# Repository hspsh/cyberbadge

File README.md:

# cyberbadge

Pin definitions:

| Name        | Pin         | Description
| ----------- | ----------- | -----------
| ESP_BOOT_B1 | 0           | Sleep / User button 1 / boot into programming mode
| PROG_TX     | 1           | 
| PROG_RX     | 3           | 
| LIPO_VMEAS  | 15          | Connected to LiPo voltage behind 2/3 divider
| WS_OUT      | 22          | WS2812 output pin
| ESP_B2      | 26          | User button 2 / boot alternative firmware
| ESP_B3      | 25          | User button 3

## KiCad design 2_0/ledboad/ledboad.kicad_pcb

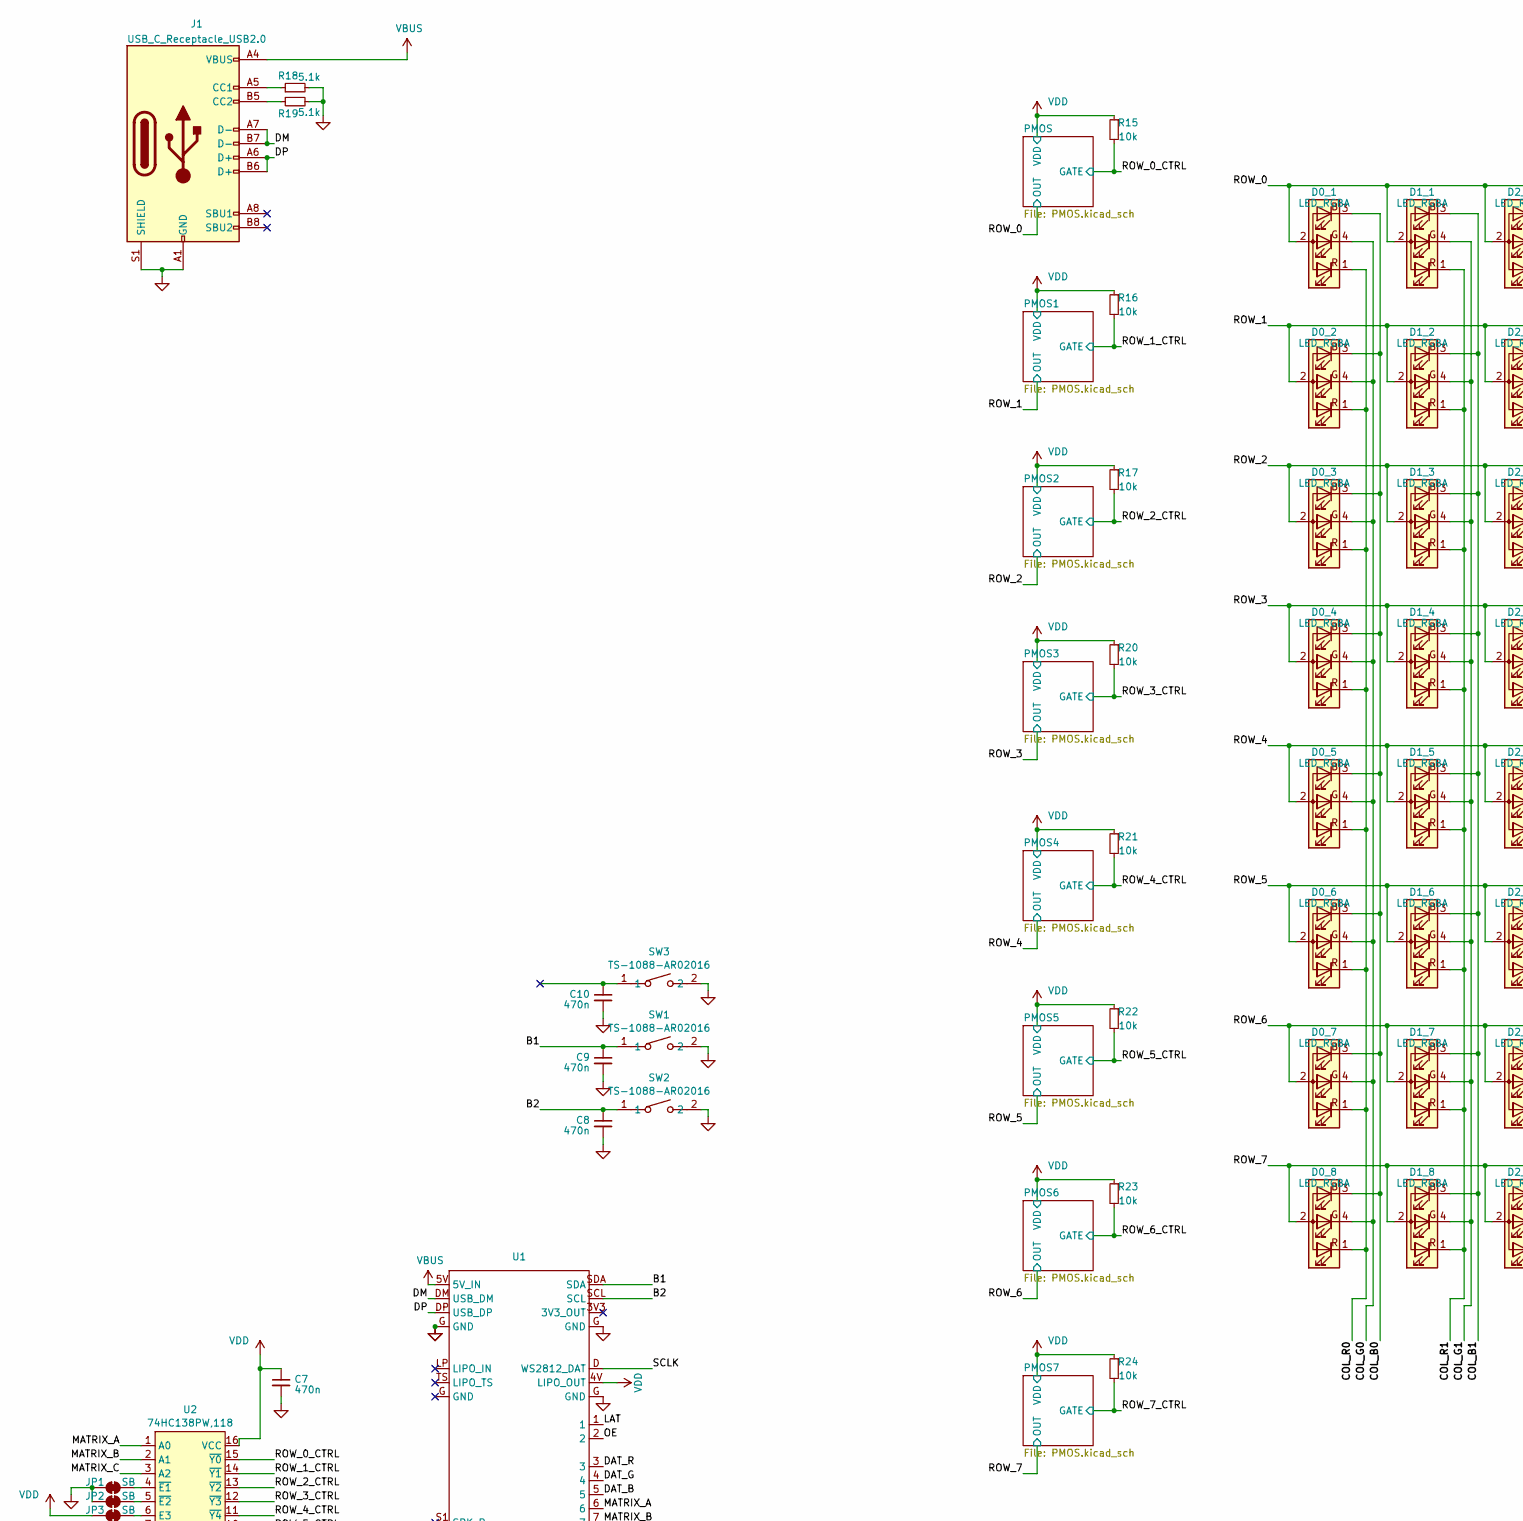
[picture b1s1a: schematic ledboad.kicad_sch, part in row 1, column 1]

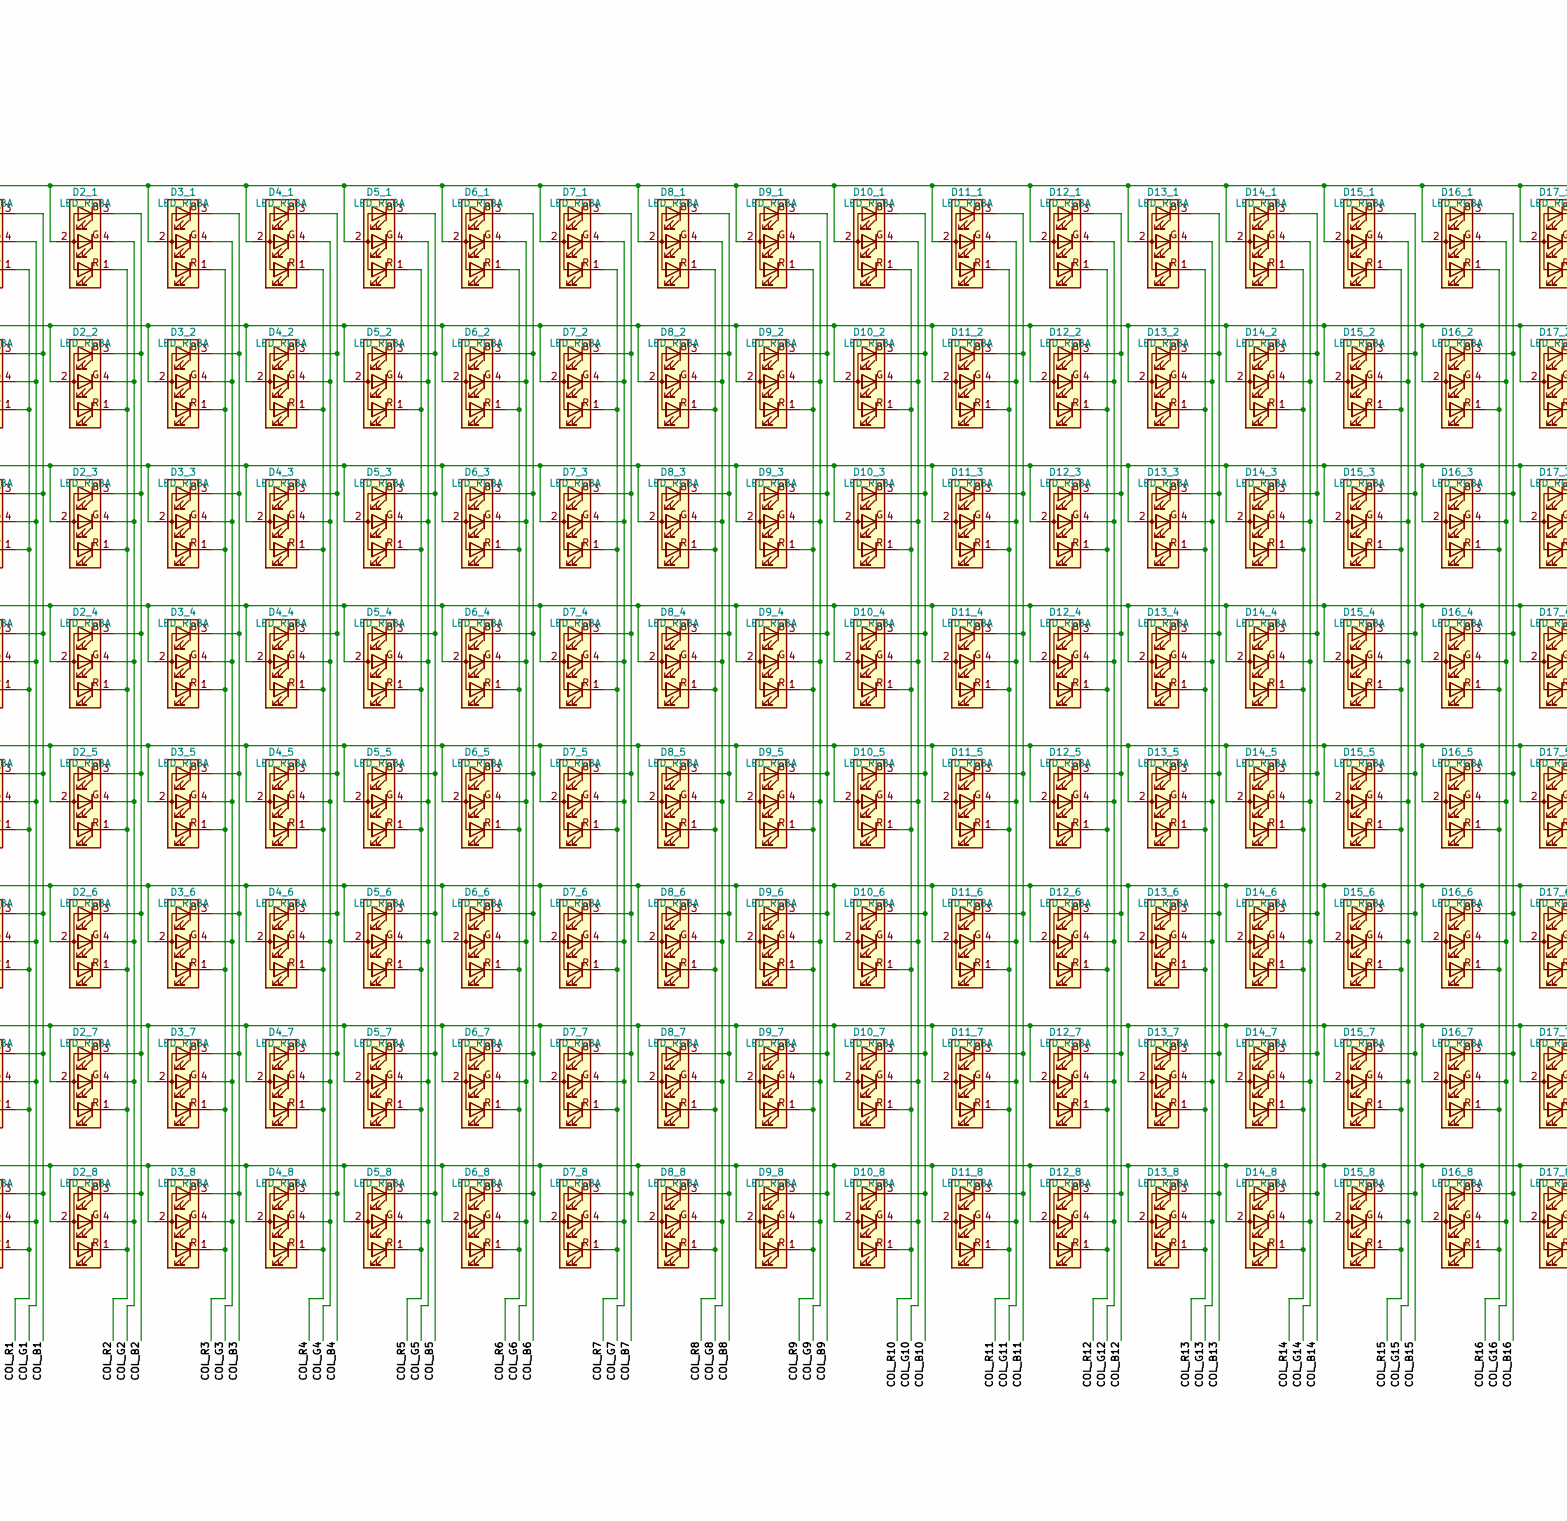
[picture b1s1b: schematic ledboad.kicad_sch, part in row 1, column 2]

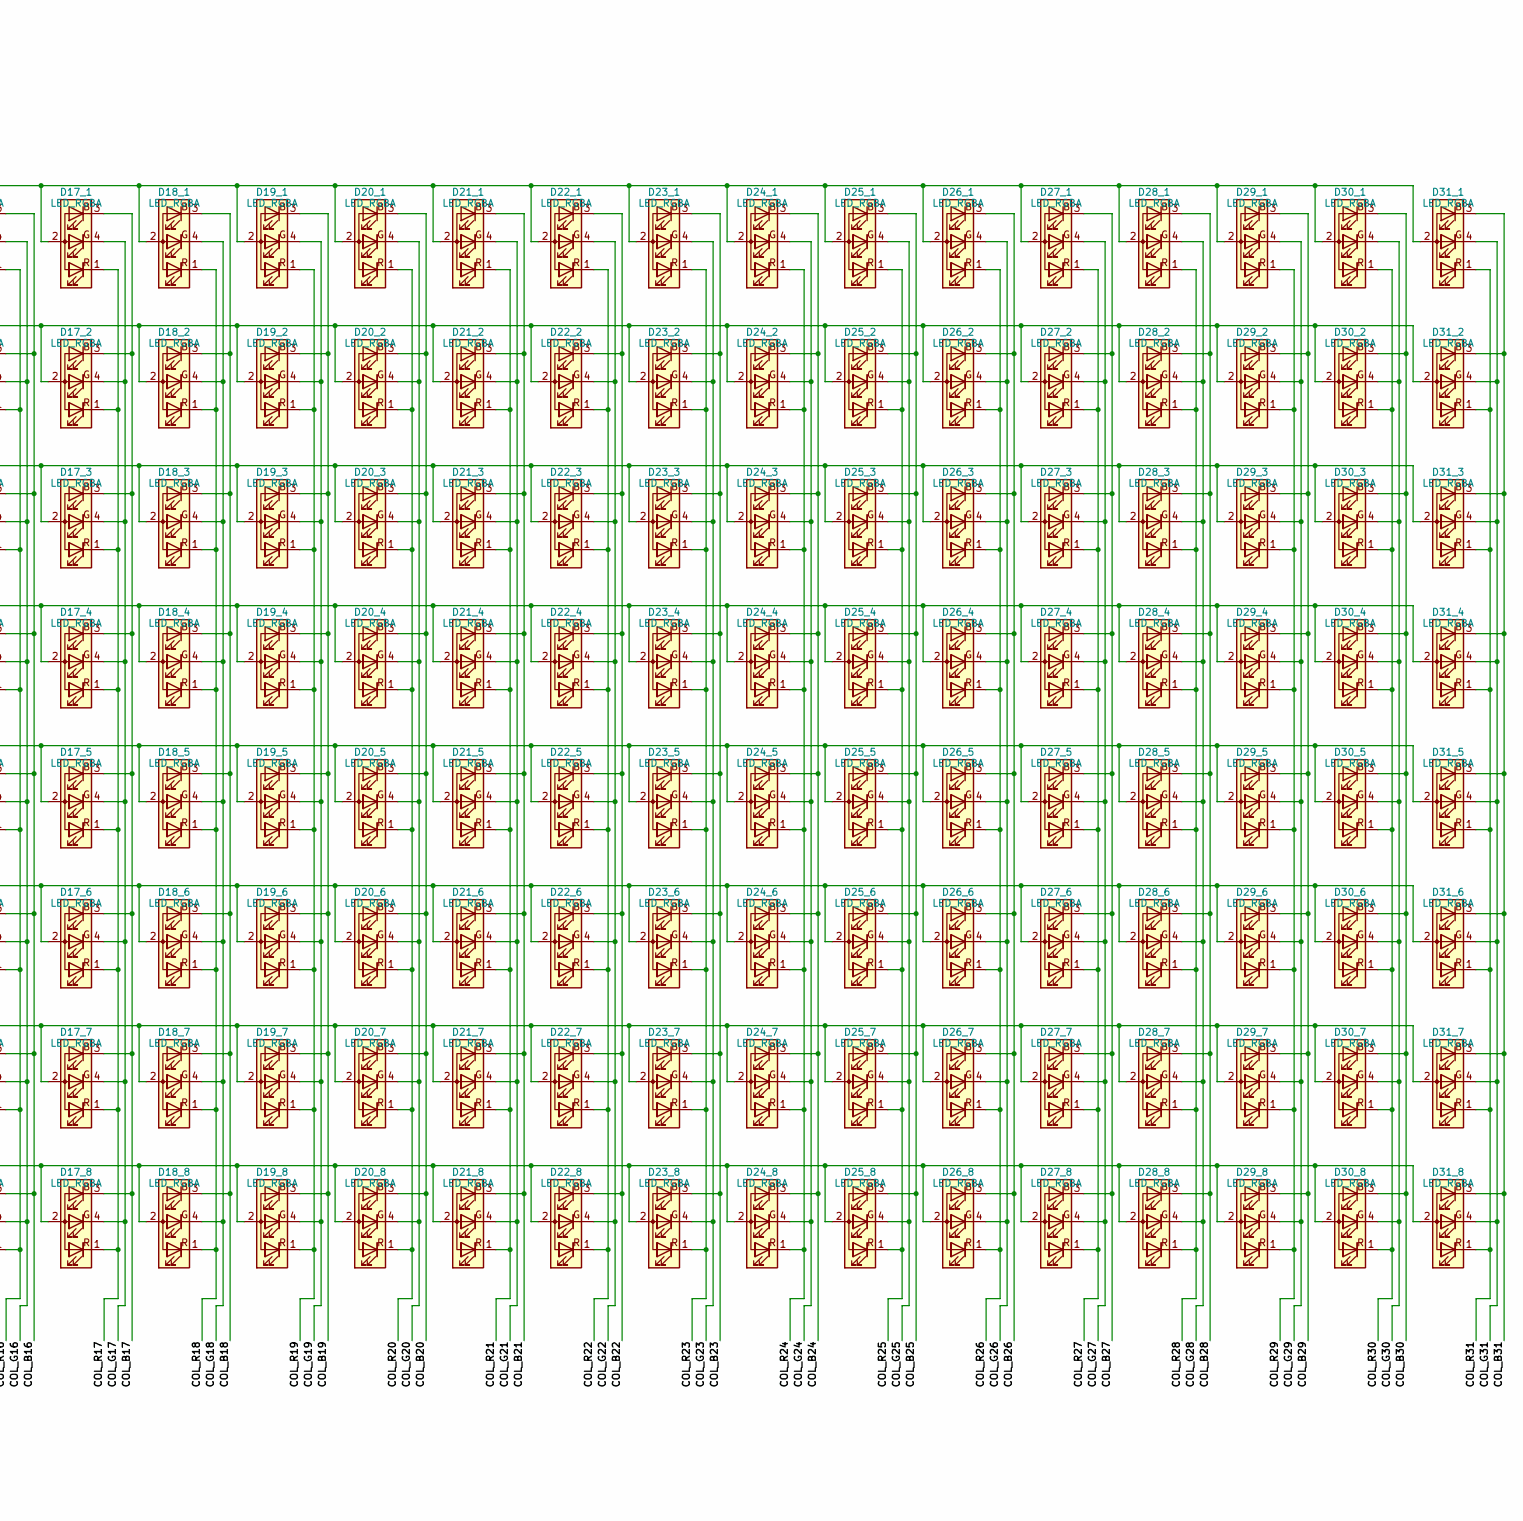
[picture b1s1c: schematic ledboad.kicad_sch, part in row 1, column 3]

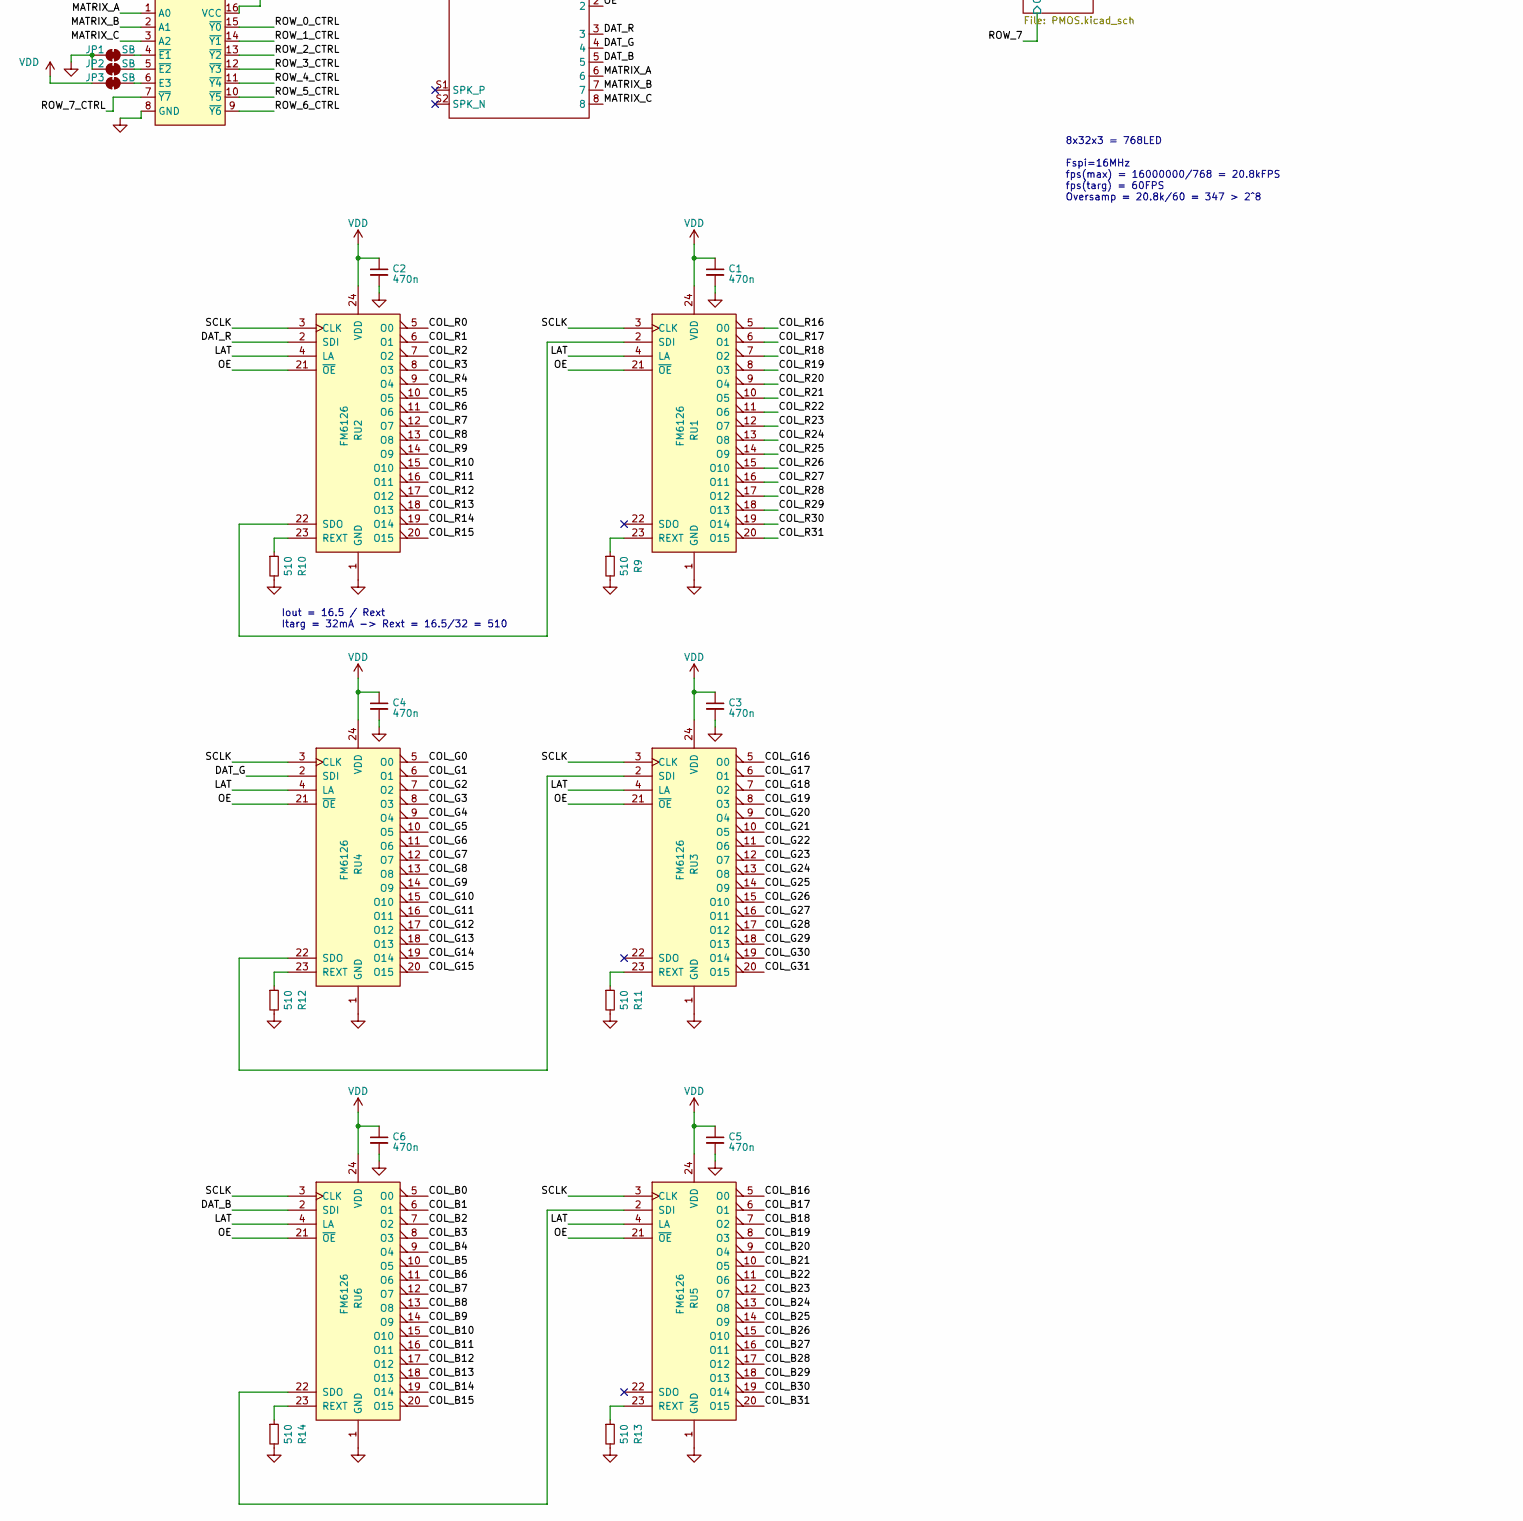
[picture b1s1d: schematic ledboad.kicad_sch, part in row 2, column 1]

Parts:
C1, C2, C3, C4, C5, C6, C7, C8, C9, C10: 470n; C_0402_1005Metric; LCSC C52923
D0_1, D0_2, D0_3, D0_4, D0_5, D0_6, D0_7, D0_8, D1_1, D1_2, D1_3, D1_4, D1_5, D1_6, D1_7, D1_8, D2_1, D2_2, D2_3, D2_4, D2_5, D2_6, D2_7, D2_8, D3_1, D3_2, D3_3, D3_4, D3_5, D3_6, D3_7, D3_8, D4_1, D4_2, D4_3, D4_4, D4_5, D4_6, D4_7, D4_8, D5_1, D5_2, D5_3, D5_4, D5_5, D5_6, D5_7, D5_8, D6_1, D6_2, D6_3, D6_4, D6_5, D6_6, D6_7, D6_8, D7_1, D7_2, D7_3, D7_4, D7_5, D7_6, D7_7, D7_8, D8_1, D8_2, D8_3, D8_4, D8_5, D8_6, D8_7, D8_8, D9_1, D9_2, D9_3, D9_4, D9_5, D9_6, D9_7, D9_8, D10_1, D10_2, D10_3, D10_4, D10_5, D10_6, D10_7, D10_8, D11_1, D11_2, D11_3, D11_4, D11_5, D11_6, D11_7, D11_8, D12_1, D12_2, D12_3, D12_4, D12_5, D12_6, D12_7, D12_8, D13_1, D13_2, D13_3, D13_4, D13_5, D13_6, D13_7, D13_8, D14_1, D14_2, D14_3, D14_4, D14_5, D14_6, D14_7, D14_8, D15_1, D15_2, D15_3, D15_4, D15_5, D15_6, D15_7, D15_8, D16_1, D16_2, D16_3, D16_4, D16_5, D16_6, D16_7, D16_8, D17_1, D17_2, D17_3, D17_4, D17_5, D17_6, D17_7, D17_8, D18_1, D18_2, D18_3, D18_4, D18_5, D18_6, D18_7, D18_8, D19_1, D19_2, D19_3, D19_4, D19_5, D19_6, D19_7, D19_8, D20_1, D20_2, D20_3, D20_4, D20_5, D20_6, D20_7, D20_8, D21_1, D21_2, D21_3, D21_4, D21_5, D21_6, D21_7, D21_8, D22_1, D22_2, D22_3, D22_4, D22_5, D22_6, D22_7, D22_8, D23_1, D23_2, D23_3, D23_4, D23_5, D23_6, D23_7, D23_8, D24_1, D24_2, D24_3, D24_4, D24_5, D24_6, D24_7, D24_8, D25_1, D25_2, D25_3, D25_4, D25_5, D25_6, D25_7, D25_8, D26_1, D26_2, D26_3, D26_4, D26_5, D26_6, D26_7, D26_8, D27_1, D27_2, D27_3, D27_4, D27_5, D27_6, D27_7, D27_8, D28_1, D28_2, D28_3, D28_4, D28_5, D28_6, D28_7, D28_8, D29_1, D29_2, D29_3, D29_4, D29_5, D29_6, D29_7, D29_8, D30_1, D30_2, D30_3, D30_4, D30_5, D30_6, D30_7, D30_8, D31_1, D31_2, D31_3, D31_4, D31_5, D31_6, D31_7, D31_8: LED_RGBA; 0606; LCSC C2874115
J1: USB_C_Receptacle_USB2.0; USB_C_Receptacle_HRO_TYPE-C-31-M-12; LCSC C165948
JP1, JP2, JP3: SB; SolderJumper-2_P1.3mm_Bridged_RoundedPad1.0x1.5mm
R9, R10, R11, R12, R13, R14: 510; R_0402_1005Metric; LCSC C25123
R15, R16, R17, R20, R21, R22, R23, R24: 10k; R_0402_1005Metric; LCSC C25744
R18, R19: 5.1k; R_0402_1005Metric; LCSC C25905
RU1, RU2, RU3, RU4, RU5, RU6: FM6126; SSOP-24_3.9x8.7mm_P0.635mm; LCSC C121618
SW1, SW2, SW3: TS-1088-AR02016; SW-SMD_L3.9-W3.0-P4.45; LCSC C720477
U1: pilkbrain2
U2: 74HC138PW,118; SSOP-16_L6.2-W5.3-P0.65-LS7.8-BL; LCSC C47455

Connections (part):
/B1: C9.1, SW1.1, U1.SDA
/B2: C8.1, SW2.1, U1.SCL
/COL_B0: D0_1.3 (BK), D0_2.3 (BK), D0_3.3 (BK), D0_4.3 (BK), D0_5.3 (BK), D0_6.3 (BK), D0_7.3 (BK), D0_8.3 (BK), RU6.5 (O0)
/COL_B1: D1_1.3 (BK), D1_2.3 (BK), D1_3.3 (BK), D1_4.3 (BK), D1_5.3 (BK), D1_6.3 (BK), D1_7.3 (BK), D1_8.3 (BK), RU6.6 (O1)
/COL_B2: D2_1.3 (BK), D2_2.3 (BK), D2_3.3 (BK), D2_4.3 (BK), D2_5.3 (BK), D2_6.3 (BK), D2_7.3 (BK), D2_8.3 (BK), RU6.7 (O2)
/COL_B3: D3_1.3 (BK), D3_2.3 (BK), D3_3.3 (BK), D3_4.3 (BK), D3_5.3 (BK), D3_6.3 (BK), D3_7.3 (BK), D3_8.3 (BK), RU6.8 (O3)
/COL_B4: D4_1.3 (BK), D4_2.3 (BK), D4_3.3 (BK), D4_4.3 (BK), D4_5.3 (BK), D4_6.3 (BK), D4_7.3 (BK), D4_8.3 (BK), RU6.9 (O4)
/COL_B5: D5_1.3 (BK), D5_2.3 (BK), D5_3.3 (BK), D5_4.3 (BK), D5_5.3 (BK), D5_6.3 (BK), D5_7.3 (BK), D5_8.3 (BK), RU6.10 (O5)
/COL_B6: D6_1.3 (BK), D6_2.3 (BK), D6_3.3 (BK), D6_4.3 (BK), D6_5.3 (BK), D6_6.3 (BK), D6_7.3 (BK), D6_8.3 (BK), RU6.11 (O6)
/COL_B7: D7_1.3 (BK), D7_2.3 (BK), D7_3.3 (BK), D7_4.3 (BK), D7_5.3 (BK), D7_6.3 (BK), D7_7.3 (BK), D7_8.3 (BK), RU6.12 (O7)
/COL_B8: D8_1.3 (BK), D8_2.3 (BK), D8_3.3 (BK), D8_4.3 (BK), D8_5.3 (BK), D8_6.3 (BK), D8_7.3 (BK), D8_8.3 (BK), RU6.13 (O8)
/COL_B9: D9_1.3 (BK), D9_2.3 (BK), D9_3.3 (BK), D9_4.3 (BK), D9_5.3 (BK), D9_6.3 (BK), D9_7.3 (BK), D9_8.3 (BK), RU6.14 (O9)
/COL_B10: D10_1.3 (BK), D10_2.3 (BK), D10_3.3 (BK), D10_4.3 (BK), D10_5.3 (BK), D10_6.3 (BK), D10_7.3 (BK), D10_8.3 (BK), RU6.15 (O10)
/COL_B11: D11_1.3 (BK), D11_2.3 (BK), D11_3.3 (BK), D11_4.3 (BK), D11_5.3 (BK), D11_6.3 (BK), D11_7.3 (BK), D11_8.3 (BK), RU6.16 (O11)
/COL_B12: D12_1.3 (BK), D12_2.3 (BK), D12_3.3 (BK), D12_4.3 (BK), D12_5.3 (BK), D12_6.3 (BK), D12_7.3 (BK), D12_8.3 (BK), RU6.17 (O12)
/COL_B13: D13_1.3 (BK), D13_2.3 (BK), D13_3.3 (BK), D13_4.3 (BK), D13_5.3 (BK), D13_6.3 (BK), D13_7.3 (BK), D13_8.3 (BK), RU6.18 (O13)
/COL_B14: D14_1.3 (BK), D14_2.3 (BK), D14_3.3 (BK), D14_4.3 (BK), D14_5.3 (BK), D14_6.3 (BK), D14_7.3 (BK), D14_8.3 (BK), RU6.19 (O14)
/COL_B15: D15_1.3 (BK), D15_2.3 (BK), D15_3.3 (BK), D15_4.3 (BK), D15_5.3 (BK), D15_6.3 (BK), D15_7.3 (BK), D15_8.3 (BK), RU6.20 (O15)
/COL_B16: D16_1.3 (BK), D16_2.3 (BK), D16_3.3 (BK), D16_4.3 (BK), D16_5.3 (BK), D16_6.3 (BK), D16_7.3 (BK), D16_8.3 (BK), RU5.5 (O0)
/COL_B17: D17_1.3 (BK), D17_2.3 (BK), D17_3.3 (BK), D17_4.3 (BK), D17_5.3 (BK), D17_6.3 (BK), D17_7.3 (BK), D17_8.3 (BK), RU5.6 (O1)
/COL_B18: D18_1.3 (BK), D18_2.3 (BK), D18_3.3 (BK), D18_4.3 (BK), D18_5.3 (BK), D18_6.3 (BK), D18_7.3 (BK), D18_8.3 (BK), RU5.7 (O2)
/COL_B19: D19_1.3 (BK), D19_2.3 (BK), D19_3.3 (BK), D19_4.3 (BK), D19_5.3 (BK), D19_6.3 (BK), D19_7.3 (BK), D19_8.3 (BK), RU5.8 (O3)
/COL_B20: D20_1.3 (BK), D20_2.3 (BK), D20_3.3 (BK), D20_4.3 (BK), D20_5.3 (BK), D20_6.3 (BK), D20_7.3 (BK), D20_8.3 (BK), RU5.9 (O4)
/COL_B21: D21_1.3 (BK), D21_2.3 (BK), D21_3.3 (BK), D21_4.3 (BK), D21_5.3 (BK), D21_6.3 (BK), D21_7.3 (BK), D21_8.3 (BK), RU5.10 (O5)
/COL_B22: D22_1.3 (BK), D22_2.3 (BK), D22_3.3 (BK), D22_4.3 (BK), D22_5.3 (BK), D22_6.3 (BK), D22_7.3 (BK), D22_8.3 (BK), RU5.11 (O6)
/COL_B23: D23_1.3 (BK), D23_2.3 (BK), D23_3.3 (BK), D23_4.3 (BK), D23_5.3 (BK), D23_6.3 (BK), D23_7.3 (BK), D23_8.3 (BK), RU5.12 (O7)
/COL_B24: D24_1.3 (BK), D24_2.3 (BK), D24_3.3 (BK), D24_4.3 (BK), D24_5.3 (BK), D24_6.3 (BK), D24_7.3 (BK), D24_8.3 (BK), RU5.13 (O8)
/COL_B25: D25_1.3 (BK), D25_2.3 (BK), D25_3.3 (BK), D25_4.3 (BK), D25_5.3 (BK), D25_6.3 (BK), D25_7.3 (BK), D25_8.3 (BK), RU5.14 (O9)
/COL_B26: D26_1.3 (BK), D26_2.3 (BK), D26_3.3 (BK), D26_4.3 (BK), D26_5.3 (BK), D26_6.3 (BK), D26_7.3 (BK), D26_8.3 (BK), RU5.15 (O10)
/COL_B27: D27_1.3 (BK), D27_2.3 (BK), D27_3.3 (BK), D27_4.3 (BK), D27_5.3 (BK), D27_6.3 (BK), D27_7.3 (BK), D27_8.3 (BK), RU5.16 (O11)
/COL_B28: D28_1.3 (BK), D28_2.3 (BK), D28_3.3 (BK), D28_4.3 (BK), D28_5.3 (BK), D28_6.3 (BK), D28_7.3 (BK), D28_8.3 (BK), RU5.17 (O12)
/COL_B29: D29_1.3 (BK), D29_2.3 (BK), D29_3.3 (BK), D29_4.3 (BK), D29_5.3 (BK), D29_6.3 (BK), D29_7.3 (BK), D29_8.3 (BK), RU5.18 (O13)
/COL_B30: D30_1.3 (BK), D30_2.3 (BK), D30_3.3 (BK), D30_4.3 (BK), D30_5.3 (BK), D30_6.3 (BK), D30_7.3 (BK), D30_8.3 (BK), RU5.19 (O14)
/COL_B31: D31_1.3 (BK), D31_2.3 (BK), D31_3.3 (BK), D31_4.3 (BK), D31_5.3 (BK), D31_6.3 (BK), D31_7.3 (BK), D31_8.3 (BK), RU5.20 (O15)
/COL_G0: D0_1.4 (GK), D0_2.4 (GK), D0_3.4 (GK), D0_4.4 (GK), D0_5.4 (GK), D0_6.4 (GK), D0_7.4 (GK), D0_8.4 (GK), RU4.5 (O0)
/COL_G1: D1_1.4 (GK), D1_2.4 (GK), D1_3.4 (GK), D1_4.4 (GK), D1_5.4 (GK), D1_6.4 (GK), D1_7.4 (GK), D1_8.4 (GK), RU4.6 (O1)
/COL_G2: D2_1.4 (GK), D2_2.4 (GK), D2_3.4 (GK), D2_4.4 (GK), D2_5.4 (GK), D2_6.4 (GK), D2_7.4 (GK), D2_8.4 (GK), RU4.7 (O2)
/COL_G3: D3_1.4 (GK), D3_2.4 (GK), D3_3.4 (GK), D3_4.4 (GK), D3_5.4 (GK), D3_6.4 (GK), D3_7.4 (GK), D3_8.4 (GK), RU4.8 (O3)
/COL_G4: D4_1.4 (GK), D4_2.4 (GK), D4_3.4 (GK), D4_4.4 (GK), D4_5.4 (GK), D4_6.4 (GK), D4_7.4 (GK), D4_8.4 (GK), RU4.9 (O4)
/COL_G5: D5_1.4 (GK), D5_2.4 (GK), D5_3.4 (GK), D5_4.4 (GK), D5_5.4 (GK), D5_6.4 (GK), D5_7.4 (GK), D5_8.4 (GK), RU4.10 (O5)
/COL_G6: D6_1.4 (GK), D6_2.4 (GK), D6_3.4 (GK), D6_4.4 (GK), D6_5.4 (GK), D6_6.4 (GK), D6_7.4 (GK), D6_8.4 (GK), RU4.11 (O6)
/COL_G7: D7_1.4 (GK), D7_2.4 (GK), D7_3.4 (GK), D7_4.4 (GK), D7_5.4 (GK), D7_6.4 (GK), D7_7.4 (GK), D7_8.4 (GK), RU4.12 (O7)
/COL_G8: D8_1.4 (GK), D8_2.4 (GK), D8_3.4 (GK), D8_4.4 (GK), D8_5.4 (GK), D8_6.4 (GK), D8_7.4 (GK), D8_8.4 (GK), RU4.13 (O8)
/COL_G9: D9_1.4 (GK), D9_2.4 (GK), D9_3.4 (GK), D9_4.4 (GK), D9_5.4 (GK), D9_6.4 (GK), D9_7.4 (GK), D9_8.4 (GK), RU4.14 (O9)
/COL_G10: D10_1.4 (GK), D10_2.4 (GK), D10_3.4 (GK), D10_4.4 (GK), D10_5.4 (GK), D10_6.4 (GK), D10_7.4 (GK), D10_8.4 (GK), RU4.15 (O10)
/COL_G11: D11_1.4 (GK), D11_2.4 (GK), D11_3.4 (GK), D11_4.4 (GK), D11_5.4 (GK), D11_6.4 (GK), D11_7.4 (GK), D11_8.4 (GK), RU4.16 (O11)
/COL_G12: D12_1.4 (GK), D12_2.4 (GK), D12_3.4 (GK), D12_4.4 (GK), D12_5.4 (GK), D12_6.4 (GK), D12_7.4 (GK), D12_8.4 (GK), RU4.17 (O12)
/COL_G13: D13_1.4 (GK), D13_2.4 (GK), D13_3.4 (GK), D13_4.4 (GK), D13_5.4 (GK), D13_6.4 (GK), D13_7.4 (GK), D13_8.4 (GK), RU4.18 (O13)
/COL_G14: D14_1.4 (GK), D14_2.4 (GK), D14_3.4 (GK), D14_4.4 (GK), D14_5.4 (GK), D14_6.4 (GK), D14_7.4 (GK), D14_8.4 (GK), RU4.19 (O14)
/COL_G15: D15_1.4 (GK), D15_2.4 (GK), D15_3.4 (GK), D15_4.4 (GK), D15_5.4 (GK), D15_6.4 (GK), D15_7.4 (GK), D15_8.4 (GK), RU4.20 (O15)
/COL_G16: D16_1.4 (GK), D16_2.4 (GK), D16_3.4 (GK), D16_4.4 (GK), D16_5.4 (GK), D16_6.4 (GK), D16_7.4 (GK), D16_8.4 (GK), RU3.5 (O0)
/COL_G17: D17_1.4 (GK), D17_2.4 (GK), D17_3.4 (GK), D17_4.4 (GK), D17_5.4 (GK), D17_6.4 (GK), D17_7.4 (GK), D17_8.4 (GK), RU3.6 (O1)
/COL_G18: D18_1.4 (GK), D18_2.4 (GK), D18_3.4 (GK), D18_4.4 (GK), D18_5.4 (GK), D18_6.4 (GK), D18_7.4 (GK), D18_8.4 (GK), RU3.7 (O2)
/COL_G19: D19_1.4 (GK), D19_2.4 (GK), D19_3.4 (GK), D19_4.4 (GK), D19_5.4 (GK), D19_6.4 (GK), D19_7.4 (GK), D19_8.4 (GK), RU3.8 (O3)
/COL_G20: D20_1.4 (GK), D20_2.4 (GK), D20_3.4 (GK), D20_4.4 (GK), D20_5.4 (GK), D20_6.4 (GK), D20_7.4 (GK), D20_8.4 (GK), RU3.9 (O4)
/COL_G21: D21_1.4 (GK), D21_2.4 (GK), D21_3.4 (GK), D21_4.4 (GK), D21_5.4 (GK), D21_6.4 (GK), D21_7.4 (GK), D21_8.4 (GK), RU3.10 (O5)
/COL_G22: D22_1.4 (GK), D22_2.4 (GK), D22_3.4 (GK), D22_4.4 (GK), D22_5.4 (GK), D22_6.4 (GK), D22_7.4 (GK), D22_8.4 (GK), RU3.11 (O6)
/COL_G23: D23_1.4 (GK), D23_2.4 (GK), D23_3.4 (GK), D23_4.4 (GK), D23_5.4 (GK), D23_6.4 (GK), D23_7.4 (GK), D23_8.4 (GK), RU3.12 (O7)
/COL_G24: D24_1.4 (GK), D24_2.4 (GK), D24_3.4 (GK), D24_4.4 (GK), D24_5.4 (GK), D24_6.4 (GK), D24_7.4 (GK), D24_8.4 (GK), RU3.13 (O8)
/COL_G25: D25_1.4 (GK), D25_2.4 (GK), D25_3.4 (GK), D25_4.4 (GK), D25_5.4 (GK), D25_6.4 (GK), D25_7.4 (GK), D25_8.4 (GK), RU3.14 (O9)
/COL_G26: D26_1.4 (GK), D26_2.4 (GK), D26_3.4 (GK), D26_4.4 (GK), D26_5.4 (GK), D26_6.4 (GK), D26_7.4 (GK), D26_8.4 (GK), RU3.15 (O10)
/COL_G27: D27_1.4 (GK), D27_2.4 (GK), D27_3.4 (GK), D27_4.4 (GK), D27_5.4 (GK), D27_6.4 (GK), D27_7.4 (GK), D27_8.4 (GK), RU3.16 (O11)
/COL_G28: D28_1.4 (GK), D28_2.4 (GK), D28_3.4 (GK), D28_4.4 (GK), D28_5.4 (GK), D28_6.4 (GK), D28_7.4 (GK), D28_8.4 (GK), RU3.17 (O12)
/COL_G29: D29_1.4 (GK), D29_2.4 (GK), D29_3.4 (GK), D29_4.4 (GK), D29_5.4 (GK), D29_6.4 (GK), D29_7.4 (GK), D29_8.4 (GK), RU3.18 (O13)
/COL_G30: D30_1.4 (GK), D30_2.4 (GK), D30_3.4 (GK), D30_4.4 (GK), D30_5.4 (GK), D30_6.4 (GK), D30_7.4 (GK), D30_8.4 (GK), RU3.19 (O14)
/COL_G31: D31_1.4 (GK), D31_2.4 (GK), D31_3.4 (GK), D31_4.4 (GK), D31_5.4 (GK), D31_6.4 (GK), D31_7.4 (GK), D31_8.4 (GK), RU3.20 (O15)
/COL_R0: D0_1.1 (RK), D0_2.1 (RK), D0_3.1 (RK), D0_4.1 (RK), D0_5.1 (RK), D0_6.1 (RK), D0_7.1 (RK), D0_8.1 (RK), RU2.5 (O0)
/COL_R1: D1_1.1 (RK), D1_2.1 (RK), D1_3.1 (RK), D1_4.1 (RK), D1_5.1 (RK), D1_6.1 (RK), D1_7.1 (RK), D1_8.1 (RK), RU2.6 (O1)
/COL_R2: D2_1.1 (RK), D2_2.1 (RK), D2_3.1 (RK), D2_4.1 (RK), D2_5.1 (RK), D2_6.1 (RK), D2_7.1 (RK), D2_8.1 (RK), RU2.7 (O2)
/COL_R3: D3_1.1 (RK), D3_2.1 (RK), D3_3.1 (RK), D3_4.1 (RK), D3_5.1 (RK), D3_6.1 (RK), D3_7.1 (RK), D3_8.1 (RK), RU2.8 (O3)
/COL_R4: D4_1.1 (RK), D4_2.1 (RK), D4_3.1 (RK), D4_4.1 (RK), D4_5.1 (RK), D4_6.1 (RK), D4_7.1 (RK), D4_8.1 (RK), RU2.9 (O4)
/COL_R5: D5_1.1 (RK), D5_2.1 (RK), D5_3.1 (RK), D5_4.1 (RK), D5_5.1 (RK), D5_6.1 (RK), D5_7.1 (RK), D5_8.1 (RK), RU2.10 (O5)
/COL_R6: D6_1.1 (RK), D6_2.1 (RK), D6_3.1 (RK), D6_4.1 (RK), D6_5.1 (RK), D6_6.1 (RK), D6_7.1 (RK), D6_8.1 (RK), RU2.11 (O6)
/COL_R7: D7_1.1 (RK), D7_2.1 (RK), D7_3.1 (RK), D7_4.1 (RK), D7_5.1 (RK), D7_6.1 (RK), D7_7.1 (RK), D7_8.1 (RK), RU2.12 (O7)
/COL_R8: D8_1.1 (RK), D8_2.1 (RK), D8_3.1 (RK), D8_4.1 (RK), D8_5.1 (RK), D8_6.1 (RK), D8_7.1 (RK), D8_8.1 (RK), RU2.13 (O8)
/COL_R9: D9_1.1 (RK), D9_2.1 (RK), D9_3.1 (RK), D9_4.1 (RK), D9_5.1 (RK), D9_6.1 (RK), D9_7.1 (RK), D9_8.1 (RK), RU2.14 (O9)
/COL_R10: D10_1.1 (RK), D10_2.1 (RK), D10_3.1 (RK), D10_4.1 (RK), D10_5.1 (RK), D10_6.1 (RK), D10_7.1 (RK), D10_8.1 (RK), RU2.15 (O10)
/COL_R11: D11_1.1 (RK), D11_2.1 (RK), D11_3.1 (RK), D11_4.1 (RK), D11_5.1 (RK), D11_6.1 (RK), D11_7.1 (RK), D11_8.1 (RK), RU2.16 (O11)
/COL_R12: D12_1.1 (RK), D12_2.1 (RK), D12_3.1 (RK), D12_4.1 (RK), D12_5.1 (RK), D12_6.1 (RK), D12_7.1 (RK), D12_8.1 (RK), RU2.17 (O12)
/COL_R13: D13_1.1 (RK), D13_2.1 (RK), D13_3.1 (RK), D13_4.1 (RK), D13_5.1 (RK), D13_6.1 (RK), D13_7.1 (RK), D13_8.1 (RK), RU2.18 (O13)
/COL_R14: D14_1.1 (RK), D14_2.1 (RK), D14_3.1 (RK), D14_4.1 (RK), D14_5.1 (RK), D14_6.1 (RK), D14_7.1 (RK), D14_8.1 (RK), RU2.19 (O14)
/COL_R15: D15_1.1 (RK), D15_2.1 (RK), D15_3.1 (RK), D15_4.1 (RK), D15_5.1 (RK), D15_6.1 (RK), D15_7.1 (RK), D15_8.1 (RK), RU2.20 (O15)
/COL_R16: D16_1.1 (RK), D16_2.1 (RK), D16_3.1 (RK), D16_4.1 (RK), D16_5.1 (RK), D16_6.1 (RK), D16_7.1 (RK), D16_8.1 (RK), RU1.5 (O0)
/COL_R17: D17_1.1 (RK), D17_2.1 (RK), D17_3.1 (RK), D17_4.1 (RK), D17_5.1 (RK), D17_6.1 (RK), D17_7.1 (RK), D17_8.1 (RK), RU1.6 (O1)
/COL_R18: D18_1.1 (RK), D18_2.1 (RK), D18_3.1 (RK), D18_4.1 (RK), D18_5.1 (RK), D18_6.1 (RK), D18_7.1 (RK), D18_8.1 (RK), RU1.7 (O2)
/COL_R19: D19_1.1 (RK), D19_2.1 (RK), D19_3.1 (RK), D19_4.1 (RK), D19_5.1 (RK), D19_6.1 (RK), D19_7.1 (RK), D19_8.1 (RK), RU1.8 (O3)
/COL_R20: D20_1.1 (RK), D20_2.1 (RK), D20_3.1 (RK), D20_4.1 (RK), D20_5.1 (RK), D20_6.1 (RK), D20_7.1 (RK), D20_8.1 (RK), RU1.9 (O4)
/COL_R21: D21_1.1 (RK), D21_2.1 (RK), D21_3.1 (RK), D21_4.1 (RK), D21_5.1 (RK), D21_6.1 (RK), D21_7.1 (RK), D21_8.1 (RK), RU1.10 (O5)
/COL_R22: D22_1.1 (RK), D22_2.1 (RK), D22_3.1 (RK), D22_4.1 (RK), D22_5.1 (RK), D22_6.1 (RK), D22_7.1 (RK), D22_8.1 (RK), RU1.11 (O6)
/COL_R23: D23_1.1 (RK), D23_2.1 (RK), D23_3.1 (RK), D23_4.1 (RK), D23_5.1 (RK), D23_6.1 (RK), D23_7.1 (RK), D23_8.1 (RK), RU1.12 (O7)
/COL_R24: D24_1.1 (RK), D24_2.1 (RK), D24_3.1 (RK), D24_4.1 (RK), D24_5.1 (RK), D24_6.1 (RK), D24_7.1 (RK), D24_8.1 (RK), RU1.13 (O8)
/COL_R25: D25_1.1 (RK), D25_2.1 (RK), D25_3.1 (RK), D25_4.1 (RK), D25_5.1 (RK), D25_6.1 (RK), D25_7.1 (RK), D25_8.1 (RK), RU1.14 (O9)
/COL_R26: D26_1.1 (RK), D26_2.1 (RK), D26_3.1 (RK), D26_4.1 (RK), D26_5.1 (RK), D26_6.1 (RK), D26_7.1 (RK), D26_8.1 (RK), RU1.15 (O10)
/COL_R27: D27_1.1 (RK), D27_2.1 (RK), D27_3.1 (RK), D27_4.1 (RK), D27_5.1 (RK), D27_6.1 (RK), D27_7.1 (RK), D27_8.1 (RK), RU1.16 (O11)
/COL_R28: D28_1.1 (RK), D28_2.1 (RK), D28_3.1 (RK), D28_4.1 (RK), D28_5.1 (RK), D28_6.1 (RK), D28_7.1 (RK), D28_8.1 (RK), RU1.17 (O12)
/COL_R29: D29_1.1 (RK), D29_2.1 (RK), D29_3.1 (RK), D29_4.1 (RK), D29_5.1 (RK), D29_6.1 (RK), D29_7.1 (RK), D29_8.1 (RK), RU1.18 (O13)
/COL_R30: D30_1.1 (RK), D30_2.1 (RK), D30_3.1 (RK), D30_4.1 (RK), D30_5.1 (RK), D30_6.1 (RK), D30_7.1 (RK), D30_8.1 (RK), RU1.19 (O14)
/COL_R31: D31_1.1 (RK), D31_2.1 (RK), D31_3.1 (RK), D31_4.1 (RK), D31_5.1 (RK), D31_6.1 (RK), D31_7.1 (RK), D31_8.1 (RK), RU1.20 (O15)
/DAT_B: RU6.2 (SDI), U1.5
/DAT_G: RU4.2 (SDI), U1.4
/DAT_R: RU2.2 (SDI), U1.3
/DM: J1.A7 (D-), J1.B7 (D-), U1.DM (USB_DM)
/DP: J1.A6 (D+), J1.B6 (D+), U1.DP (USB_DP)
/LAT: RU1.4 (LA), RU2.4 (LA), RU3.4 (LA), RU4.4 (LA), RU5.4 (LA), RU6.4 (LA), U1.1
/MATRIX_A: U1.6, U2.1 (A0)
/MATRIX_B: U1.7, U2.2 (A1)
/MATRIX_C: U1.8, U2.3 (A2)
/OE: RU1.21 (~OE), RU2.21 (~OE), RU3.21 (~OE), RU4.21 (~OE), RU5.21 (~OE), RU6.21 (~OE), U1.2
/ROW_0: D0_1.2 (A), D1_1.2 (A), D2_1.2 (A), D3_1.2 (A), D4_1.2 (A), D5_1.2 (A), D6_1.2 (A), D7_1.2 (A), D8_1.2 (A), D9_1.2 (A), D10_1.2 (A), D11_1.2 (A), D12_1.2 (A), D13_1.2 (A), D14_1.2 (A), D15_1.2 (A), D16_1.2 (A), D17_1.2 (A), D18_1.2 (A), D19_1.2 (A), D20_1.2 (A), D21_1.2 (A), D22_1.2 (A), D23_1.2 (A), D24_1.2 (A), D25_1.2 (A), D26_1.2 (A), D27_1.2 (A), D28_1.2 (A), D29_1.2 (A), D30_1.2 (A), D31_1.2 (A); also elsewhere on the board
/ROW_0_CTRL: R15.2, U2.15 (~Y0); also elsewhere on the board
/ROW_1: D0_2.2 (A), D1_2.2 (A), D2_2.2 (A), D3_2.2 (A), D4_2.2 (A), D5_2.2 (A), D6_2.2 (A), D7_2.2 (A), D8_2.2 (A), D9_2.2 (A), D10_2.2 (A), D11_2.2 (A), D12_2.2 (A), D13_2.2 (A), D14_2.2 (A), D15_2.2 (A), D16_2.2 (A), D17_2.2 (A), D18_2.2 (A), D19_2.2 (A), D20_2.2 (A), D21_2.2 (A), D22_2.2 (A), D23_2.2 (A), D24_2.2 (A), D25_2.2 (A), D26_2.2 (A), D27_2.2 (A), D28_2.2 (A), D29_2.2 (A), D30_2.2 (A), D31_2.2 (A); also elsewhere on the board
/ROW_1_CTRL: R16.2, U2.14 (~Y1); also elsewhere on the board
/ROW_2: D0_3.2 (A), D1_3.2 (A), D2_3.2 (A), D3_3.2 (A), D4_3.2 (A), D5_3.2 (A), D6_3.2 (A), D7_3.2 (A), D8_3.2 (A), D9_3.2 (A), D10_3.2 (A), D11_3.2 (A), D12_3.2 (A), D13_3.2 (A), D14_3.2 (A), D15_3.2 (A), D16_3.2 (A), D17_3.2 (A), D18_3.2 (A), D19_3.2 (A), D20_3.2 (A), D21_3.2 (A), D22_3.2 (A), D23_3.2 (A), D24_3.2 (A), D25_3.2 (A), D26_3.2 (A), D27_3.2 (A), D28_3.2 (A), D29_3.2 (A), D30_3.2 (A), D31_3.2 (A); also elsewhere on the board
/ROW_2_CTRL: R17.2, U2.13 (~Y2); also elsewhere on the board
/ROW_3: D0_4.2 (A), D1_4.2 (A), D2_4.2 (A), D3_4.2 (A), D4_4.2 (A), D5_4.2 (A), D6_4.2 (A), D7_4.2 (A), D8_4.2 (A), D9_4.2 (A), D10_4.2 (A), D11_4.2 (A), D12_4.2 (A), D13_4.2 (A), D14_4.2 (A), D15_4.2 (A), D16_4.2 (A), D17_4.2 (A), D18_4.2 (A), D19_4.2 (A), D20_4.2 (A), D21_4.2 (A), D22_4.2 (A), D23_4.2 (A), D24_4.2 (A), D25_4.2 (A), D26_4.2 (A), D27_4.2 (A), D28_4.2 (A), D29_4.2 (A), D30_4.2 (A), D31_4.2 (A); also elsewhere on the board
/ROW_3_CTRL: R20.2, U2.12 (~Y3); also elsewhere on the board
/ROW_4: D0_5.2 (A), D1_5.2 (A), D2_5.2 (A), D3_5.2 (A), D4_5.2 (A), D5_5.2 (A), D6_5.2 (A), D7_5.2 (A), D8_5.2 (A), D9_5.2 (A), D10_5.2 (A), D11_5.2 (A), D12_5.2 (A), D13_5.2 (A), D14_5.2 (A), D15_5.2 (A), D16_5.2 (A), D17_5.2 (A), D18_5.2 (A), D19_5.2 (A), D20_5.2 (A), D21_5.2 (A), D22_5.2 (A), D23_5.2 (A), D24_5.2 (A), D25_5.2 (A), D26_5.2 (A), D27_5.2 (A), D28_5.2 (A), D29_5.2 (A), D30_5.2 (A), D31_5.2 (A); also elsewhere on the board
/ROW_4_CTRL: R21.2, U2.11 (~Y4); also elsewhere on the board
/ROW_5: D0_6.2 (A), D1_6.2 (A), D2_6.2 (A), D3_6.2 (A), D4_6.2 (A), D5_6.2 (A), D6_6.2 (A), D7_6.2 (A), D8_6.2 (A), D9_6.2 (A), D10_6.2 (A), D11_6.2 (A), D12_6.2 (A), D13_6.2 (A), D14_6.2 (A), D15_6.2 (A), D16_6.2 (A), D17_6.2 (A), D18_6.2 (A), D19_6.2 (A), D20_6.2 (A), D21_6.2 (A), D22_6.2 (A), D23_6.2 (A), D24_6.2 (A), D25_6.2 (A), D26_6.2 (A), D27_6.2 (A), D28_6.2 (A), D29_6.2 (A), D30_6.2 (A), D31_6.2 (A); also elsewhere on the board
/ROW_5_CTRL: R22.2, U2.10 (~Y5); also elsewhere on the board
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
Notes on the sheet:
https://www.lcsc.com/product-detail/Light-Emitting-Diodes-LED_Foshan-NationStar-Optoelectronics-NH-B1515RGBA-HF_C2874115.html
Iout = 16.5 / Rext Itarg = 32mA -> Rext = 16.5/32 = 510
8x32x3 = 768LED Fspi=16MHz fps(max) = 16000000/768 = 20.8kFPS fps(targ) = 60FPS Oversamp = 20.8k/60 = 347 > 2^8

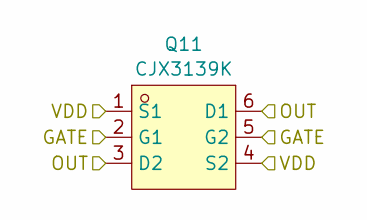
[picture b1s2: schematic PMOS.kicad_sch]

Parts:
Q11: CJX3139K; SOT-563_L1.6-W1.2-P0.50-LS1.6-BR; LCSC C504144

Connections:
/ROW_2: Q11.3 (D2), Q11.6 (D1); also elsewhere on the board
/ROW_2_CTRL: Q11.2 (G1), Q11.5 (G2); also elsewhere on the board
VDD: Q11.1 (S1), Q11.4 (S2); also elsewhere on the board

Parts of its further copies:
Q9, Q10, Q12, Q13, Q14, Q15, Q16: CJX3139K; SOT-563_L1.6-W1.2-P0.50-LS1.6-BR; LCSC C504144

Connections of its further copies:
/ROW_0: Q9.3 (D2), Q9.6 (D1); also elsewhere on the board
/ROW_0_CTRL: Q9.2 (G1), Q9.5 (G2); also elsewhere on the board
/ROW_1: Q10.3 (D2), Q10.6 (D1); also elsewhere on the board
/ROW_1_CTRL: Q10.2 (G1), Q10.5 (G2); also elsewhere on the board
/ROW_3: Q12.3 (D2), Q12.6 (D1); also elsewhere on the board
/ROW_3_CTRL: Q12.2 (G1), Q12.5 (G2); also elsewhere on the board
/ROW_4: Q13.3 (D2), Q13.6 (D1); also elsewhere on the board
/ROW_4_CTRL: Q13.2 (G1), Q13.5 (G2); also elsewhere on the board
/ROW_5: Q14.3 (D2), Q14.6 (D1); also elsewhere on the board
/ROW_5_CTRL: Q14.2 (G1), Q14.5 (G2); also elsewhere on the board
/ROW_6: Q15.3 (D2), Q15.6 (D1); also elsewhere on the board
/ROW_6_CTRL: Q15.2 (G1), Q15.5 (G2); also elsewhere on the board
/ROW_7: Q16.3 (D2), Q16.6 (D1); also elsewhere on the board
/ROW_7_CTRL: Q16.2 (G1), Q16.5 (G2); also elsewhere on the board
VDD: Q9.1 (S1), Q9.4 (S2), Q10.1 (S1), Q10.4 (S2), Q12.1 (S1), Q12.4 (S2), Q13.1 (S1), Q13.4 (S2), Q14.1 (S1), Q14.4 (S2), Q15.1 (S1), Q15.4 (S2), Q16.1 (S1), Q16.4 (S2); also elsewhere on the board

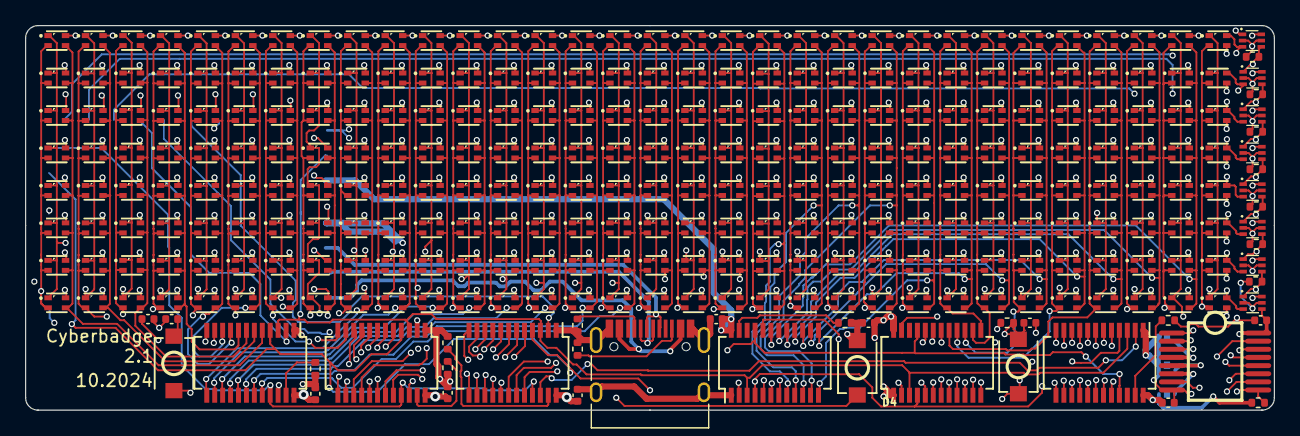
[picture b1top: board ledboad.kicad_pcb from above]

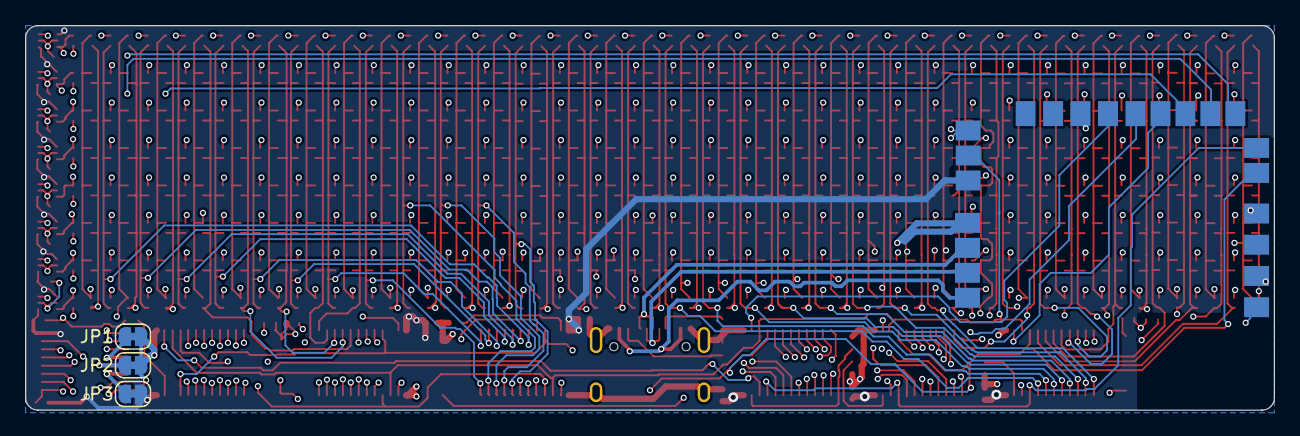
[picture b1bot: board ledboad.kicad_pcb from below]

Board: 4 copper layers, 100.0 x 30.8 mm, 305 parts (4 on the bottom side), 142 nets.
